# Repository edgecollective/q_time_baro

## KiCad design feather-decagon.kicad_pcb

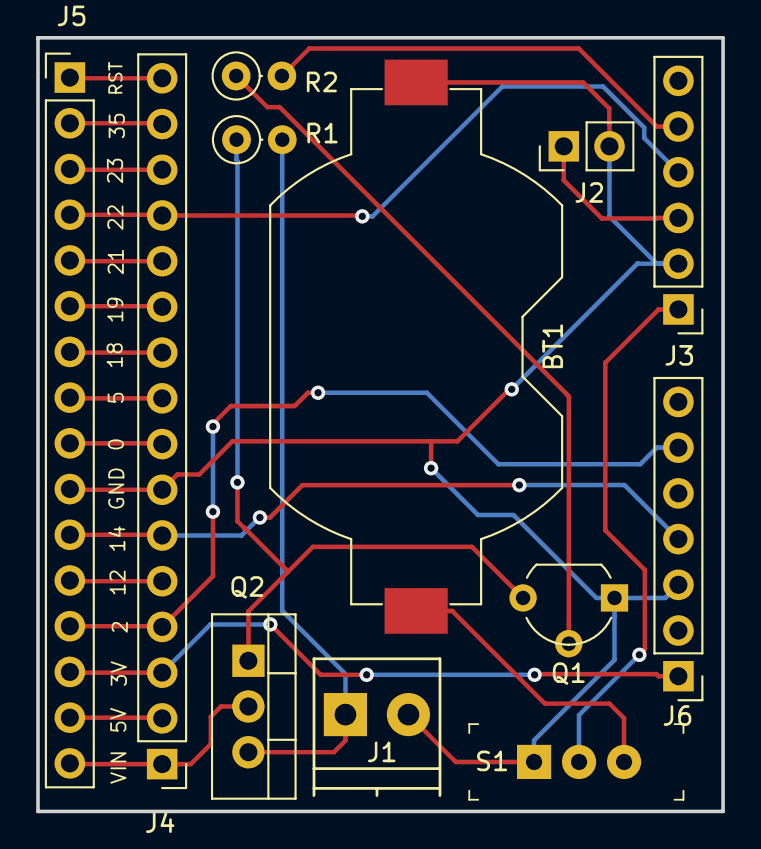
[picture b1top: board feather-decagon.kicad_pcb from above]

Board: 2 copper layers, 38.1 x 43.0 mm, 12 parts (0 on the bottom side), 23 nets.

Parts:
BT1: Battery_Cell; Keystone_1058_1x2032-CoinCell
J1: Screw_Terminal_01x02; TerminalBlock_Phoenix_PT-3.5mm_2pol
J2: Conn_01x02; Pin_Header_Straight_1x02_Pitch2.54mm
J3: tpl5110; Pin_Header_Straight_1x06_Pitch2.54mm
J4, J5: Conn_01x16; Pin_Header_Straight_1x16_Pitch2.54mm
J6: Conn_01x07; Pin_Header_Straight_1x07_Pitch2.54mm
Q1: Q_NPN_EBC; TO-92_Molded_Wide
Q2: Q_PMOS_GDS; TO-220-3_Vertical
R1: 100K; R_Axial_DIN0207_L6.3mm_D2.5mm_P2.54mm_Vertical
R2: 10K; R_Axial_DIN0207_L6.3mm_D2.5mm_P2.54mm_Vertical
S1: EG1218; Switch_Slide_11.6x4mm_EG1218

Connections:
GND: BT1.2, J1.2, J2.2, J3.2, J4.7, J5.10, J6.3, Q1.1, S1.1
unnamed: BT1.1, S1.3
unnamed: J1.1, Q2.3, R1.2
unnamed: J2.1, J3.3
unnamed: J3.1, S1.2
unnamed: J3.4, J4.13, J5.4
unnamed: J3.5, R2.2
unnamed: J4.1, J5.16, Q2.2
unnamed: J4.2, J5.15
unnamed: J4.3, J5.14, J6.1
unnamed: J4.4, J5.13, J6.6
unnamed: J4.5, J5.12
unnamed: J4.6, J5.11, J6.4
unnamed: J4.8, J5.9
unnamed: J4.9, J5.8
unnamed: J4.10, J5.7
unnamed: J4.11, J5.6
unnamed: J4.12, J5.5
unnamed: J4.14, J5.3
unnamed: J4.15, J5.2
unnamed: J4.16, J5.1
unnamed: Q1.2, R2.1
unnamed: Q1.3, Q2.1, R1.1
